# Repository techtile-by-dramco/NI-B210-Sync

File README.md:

# Methods to synchronise NI B210s for MIMO operation

This repository contains the B210 synchronization research code, hardware notes, and reproducible experiments. Start with the [experiment index](experiments/readme.md). The new RF work uses T04 as the common source and T05–T08 as the devices under test; it is split into state characterization (`50`), controlled coherent combining (`51`), and stability/recalibration events (`52`). Experiment `60` separately measures the ZMQ-to-Raspberry-Pi GPIO-arrival spread on one shared scope timebase. Each directory has a connection-first README and a `--dry-run` mode.

Repository layout:

- `experiments/` — acquisition, processing, results, and testbench instructions;
- `phased-locked-loop/` — PLL hardware, firmware, and control scripts;
- `octoclock-validation/` — reference-distribution validation;
- `software/` and `tests/` — prototypes and lower-level tests; and
- `manuscript/` — separate Overleaf Git checkout, intentionally ignored by this repository.

## Relevant sources
- [Synchronizing multiple AD9361 devices](https://wiki.analog.com/resources/eval/user-guides/ad-fmcomms5-ebz/multi-chip-sync?force_rev=1)
- [AD9361 Register Map Reference Manual](https://usermanual.wiki/Document/AD9361RegisterMapReferenceManualUG671.1082447504)
- [AD9361 Reference Manual (e.g., PLL architecture)](https://www.farnell.com/datasheets/2007082.pdf)
- [Schematic B210](https://files.ettus.com/schematics/b200/b210.pdf)
- [Schemetic octoclock CDA2990](https://files.ettus.com/schematics/octoclock/octoclock.pdf)
- [Ettus Research USRP FPGA HDL Source](https://github.com/EttusResearch/fpga)
- [AD community question related to phase diff](https://ez.analog.com/wide-band-rf-transceivers/design-support/f/q-a/543540/phase-difference-in-ad9361-multichip-synchronization)
- [Fractional/Integer-N PLL Basics](https://www.ti.com/lit/an/swra029/swra029.pdf)
- [FMComms5 Phase Synchronization](https://wiki.analog.com/resources/eval/user-guides/ad-fmcomms5-ebz/phase-sync)
- [Phase Difference in AD9361 Multichip Synchronization](https://ez.analog.com/wide-band-rf-transceivers/design-support/f/q-a/543540/phase-difference-in-ad9361-multichip-synchronization)
- [UHD Device synchronisation](https://files.ettus.com/manual/page_sync.html)
- [Timed commands in UHD](https://kb.ettus.com/index.php?title=Synchronizing_USRP_Events_Using_Timed_Commands_in_UHD)
- [DoA and methods to phase-align](https://www.youtube.com/watch?v=_UBPVi1vp2s&ab_channel=GNURadio)
- [Multichannel RF Reference Architecture](https://kb.ettus.com/Multichannel_RF_Reference_Architecture)
- [PLL-IC with phase synchronization](https://ez.analog.com/rf/f/q-a/165960/pll-ic-with-phase-synchronization/375973) (difference between sync and resync PLLs)
- [Phase-Locked Loops Enable Phase Alignment and Control](https://www.microwavejournal.com/articles/28830-phase-locked-loops-enable-phase-alignment-and-control)

## Relevant scientific publications
- [Multi-channel RF signal acquisition system design based on AD9361](https://ieeexplore.ieee.org/stamp/stamp.jsp?tp=&arnumber=9173310)
- [Angle of arrival estimation in a multi-antenna software defined radio system: impact of hardware and radio environment](https://link.springer.com/article/10.1007/s11276-022-03010-z)

## What needs to be synchronised for MIMO applications

At the RF transceiver:
- ADC/DAC sample clock
- RF mixer 
- Baseband digital clocks

At the FPGA:
- DSP (CORDICs)

Between FPGA and host:
- USB (to be checked)

At the host:

## Maintaining phase coherency at different PLLs

From [ref](https://ez.analog.com/cfs-file/__key/telligent-evolution-components-attachments/00-333-01-00-00-24-69-46/attachment.pdf):
Phase coherence is defined as the state in which two signals maintain a fixed phase relationship
between each other and is typically required for evaluating the performance of phased-array antennas
as well as for test and measurement equipment.
For integer-N PLLs, it is relatively straightforward to achieve phase coherence between multiple PLLs
by using the same reference for each PLL and updating each device at the same time to ensure the
PLL counters are aligned. This is often achieved by updating the PLL register contents with the new
frequency word while holding the device in reset. To ensure both parts get updated at the same time,
the reset signal is made common and so is cleared internally in the PLLs at exactly the same time.
This ensures the internal dividers in the PLL start counting from the same start-point. See here for a
good reference on achieving integer-N PLL phase coherence using this method. If the output
frequencies on both parts are updated at the same time then the consistent output phase will be
maintained between the multiple PLLs. To achieve absolute phase consistency with respect to the
reference input requires you to update the PLLs at a rate equal to an integer multiple of N-divide (PLL
feedback divider) times REFIN cycles. This would mean the reset signal would need to be
synchronized with the reference and a count done internally in a microcontroller to keep
synchronization. In many cases the absolute phase consistency is not required just that the relative
phase between the PLL outputs is kept constant. In this case LE can be asynchronous to the reference
input.

## B210

Sync input:
- pulse per second input: PPS_IN_EXT (see [Schematic B210](https://files.ettus.com/schematics/b200/b210.pdf))
- 20MHz reference input (as no GPS option to our B210): REFIN (see [Schematic B210](https://files.ettus.com/schematics/b200/b210.pdf))

The REFIN is connected to the [ADF4001](https://www.analog.com/en/products/adf4001.html) (200MHz Clock Generator PLL) which generates vcxo_tune which is connected to Voltage Controlled Temperature Compensated Crystal Oscillator (VCTCXO), which is than connected to a fan-out buffer to distribute it to xo_out (going to the AD9361) and xo_to_pll (to PLL RF in).

PPS_IN_EXT is connected to the Spartan6 IO_L34P_GCLK19_0.

PLL bring-up:
1. VCTCXO starts up
2. FX3 brings up transceiver, sets CLKOUT to FPGA
3. FX3 programs FPGA
4. FPGA writes to PLL, initializes PLL
5. PLL locks to external ref if avail.
6. If no ref, PLL tristated via SPI

## AD9361 - RF transceiver

As can be observed in the register manual and the [code](https://github.com/EttusResearch/uhd/blob/197cdc4f665cbd4e6394a7eeb44b405f67ab10b1/host/lib/usrp/common/ad9361_driver/ad9361_device.cpp#L1640). The BBPLL is unaltered wrt the reference PLL (40MHz) and RX and TX is multiplied by 2.
[AD9361 Register Map Reference Manual](https://usermanual.wiki/Document/AD9361RegisterMapReferenceManualUG671.1082447504)

### XTALN
The on-board 40MHz clock signal generated from the [ADF4001](https://www.analog.com/en/products/adf4001.html) is coherent:

### Synchronise ADC/DAC clocks
The ADC and DAC clocks can not be perfectly synchronised due to the divider, both clocks are derived from the same BBPLL.

$$ADC_{rate} = BBPLL_{rate} / 2^{div}$$

witd $div$ between 1 through 6. The value for $div$ is [determined so the the VCO rate is between 672MHz and 1430MHz](https://github.com/EttusResearch/uhd/blob/197cdc4f665cbd4e6394a7eeb44b405f67ab10b1/host/lib/usrp/common/ad9361_driver/ad9361_device.cpp#L1202).

The device utilizes a fractional-N synthesizer in the baseband PLL block to generate the desired sample rate for a given system. This synthesizer generates the ADC sample clock, DAC sample clock, and baseband digital clocks from any reference clock in the frequency range specified for the reference clock input.

## Sync BBPLLs and Digital CLK [AD9361 Register Map Reference Manual](https://usermanual.wiki/Document/AD9361RegisterMapReferenceManualUG671.1082447504)
  - SPI Register 0x001—Multichip Sync and Tx Monitor Control
  - D2—MCS BBPLL EnableTo synchronize the BBPLLs of multiple devices, write this bit high and then provide a sync pulse to SYNC_IN.
  - D1—MCS Digital CLK Enable To synchronize the digital clocks of multiple AD9361 devices, first synchronize the BBPLLs, then write this bit high and provide a sync pulse to the `SYNC_IN` pin. 
  - D0—MCS BB Enable Setting this bit enables the capability of baseband multichip digital synchronization. See also 0x001[D2:D1]. 

### Clock input options (from AD9361 datasheet)
The AD9361 operates using a reference clock that can be provided
by two different sources. The first option is to use a dedicated
crystal with a frequency between 19 MHz and 50 MHz connected
between the XTALP and XTALN pins. The second option is to
connect an external oscillator or clock distribution device (such as
the AD9548) to the XTALN pin (with the XTALP pin remaining
unconnected). If an external oscillator is used, the frequency
can vary between 10 MHz and 80 MHz. This reference clock
is used to supply the synthesizer blocks that generate all data
clocks, sample clocks, and local oscillators inside the device.
Errors in the crystal frequency can be removed by using the
digitally programmable digitally controlled crystal oscillator
(DCXO) function to adjust the on-chip variable capacitor. This
capacitor can tune the crystal frequency variance out of the
system, resulting in a more accurate reference clock from which
all other frequency signals are generated. This function can also
be used with on-chip temperature sensing to provide oscillator
frequency temperature compensation during normal operation.

### RF PLLs (from AD9361 datasheet)
The AD9361 contains two identical synthesizers to generate the
required LO signals for the RF signal paths:—one for the receiver
and one for the transmitter. Phase-locked loop (PLL) synthesizers
are fractional-N designs incorporating completely integrated
voltage controlled oscillators (VCOs) and loop filters. In TDD
operation, the synthesizers turn on and off as appropriate for the
RX and TX frames. In FDD mode, the TX PLL and the RX PLL
can be activated simultaneously. These PLLs require no external
components

#### RFPLL frequency

Scaling to [2xREF](https://github.com/EttusResearch/uhd/blob/197cdc4f665cbd4e6394a7eeb44b405f67ab10b1/host/lib/usrp/common/ad9361_driver/ad9361_device.cpp#L1640).
By setting registers `0x2AB` and `0x2AC`.

Meaning the RFPLL (F_{REF}) for TX and RX is 80MHz.

### BB PLL (from AD9361 datasheet)
The AD9361 also contains a baseband PLL synthesizer that is
used to generate all baseband related clock signals. These include
the ADC and DAC sampling clocks, the DATA_CLK signal (see
the Digital Data Interface section), and all data framing signals.
This PLL is programmed from 700 MHz to 1400 MHz based on
the data rate and sample rate requirements of the system. 

## FPGA

From [here](https://www.ni.com/nl-nl/shop/wireless-design-test/what-is-a-usrp-software-defined-radio/global-synchronization-and-clock-disciplining-with-ni-usrp-293x-.html):
- The USRP hardware OSP interpolates and up-converts the synthesized signals to 400 MS/s using a digital up conversion process, and uses the CORDIC algorithm to apply minor frequency offset corrections to achieve the requested RF center frequency. 
- The digitized I and Q data flow through parallel onboard signal processing (OSP) processes that applies DC offset correction and digital down conversion using the CORDIC algorithm.

[How to sync the CORDICs](https://files.ettus.com/manual/page_sync.html)

## UHD and GNURadio

There are four key elements required for phase coherent operation of resync-capable USRPs:

1. All USRPs share a common reference clock (10MHz Ref)
2. All USRPs share a common sense of time (PPS)
3. LO and DSP tuning is synchronous
4. Streaming is started synchronously

### Enable external PPS and 10MHz
```cpp
usrp->set_clock_source("external");
usrp->set_time_source("external");
```

### Defining a common absolute reference clock
The time can be 're'-set once a new PPS has occured:
```cpp
const uhd::time_spec_t last_pps_time = usrp->get_time_last_pps();
while (last_pps_time == usrp->get_time_last_pps()){
    //sleep 100 milliseconds (give or take)
}
// This command will be processed fairly soon after the last PPS edge:
usrp->set_time_next_pps(uhd::time_spec_t(0.0));

std::this_thread::sleep_for(std::chrono::milliseconds(1000));
```
After we reset the USRP's sense of time, we wait 1 second to ensure a PPS rising edge occurs and latches the 0.000s value to both USRPs. At this point, both USRPs should have a shared sense of time.  We've now satisfied the first and second requirements for phase coherent USRP operation. 

**TODO**: Send a command from the server to the RPIs to start resetting their time reference on next PPS. Or only start transmitting PPS signals from the octoclocks once all devices are operational (not sure the latter is supported by the Octoclock). 

### Timed commands for predicatable and repeatable phase offsets
```cp
usrp->clear_command_time();

usrp->set_command_time(usrp->get_time_now() + uhd::time_spec_t(0.1)); //set cmd time for .1s in the future

uhd::tune_request_t tune_request(freq);
usrp->set_rx_freq(tune_request);
std::this_thread::sleep_for(std::chrono::milliseconds(110)); //sleep 110ms (~10ms after retune occurs) to allow LO to lock

usrp->clear_command_time();
```
With the above code block, we are able to set a command time equal to the current time + 0.1s. Any commands that are called after `set_command_time()` will be sent to the USRP with a timestamp corresponding to the argument passed to `set_command_time()`. Because of this timestamp, the USRP will wait until the command time passes to execute the tune request. This will ensure that the LO and DSP chain of our USRPs are retuned synchronously (on the same clock cycle), satisfying the third requirement for phase coherent operation, i.e., LO and DSP tuning is synchronous.

Modern USRPs pass packets using the CHDR protocol. These packets can be used to issue commands to the USRP and may have an associated timestamp. A command with an included timestamp is called a timed command and it's important to understand how the USRP handles these timed commands. All blocks in a USRP's FPGA have a command queue and maintain a sense of time, however the Radio Core has the unique ability to store an absolute sense of time known as the vita_time. When timed commands are issued to the USRP, they are added to a command FIFO of finite depth and are executed when the timestamp in the header of the command packet is >= the RFNoC block's sense of time. Utilizing these timed commands correctly allows for various USRP functionality to be executed with nanosecond precision, enabling time and phase coherent operation across multiple devices.

#### Command Queue
As commands are passed from host to USRP, they are added to a FIFO on the USRP's FPGA. This FIFO is called the command queue and all commands that are sent to the USRP must pass through a command queue. Each block in the FPGA that handles data also has its own command queue. The command queue FIFO is not to be confused with the data FIFOs used to buffer data between blocks (pictured in Figure 3).

Every command queue maintains a sense of time. The mechanism for acquiring this sense of time is different between the Radio Core and other IP cores (including custom RFNoC blocks) and will be explored later in this application note. When commands enter the command queue, their timestamp is compared against the command queue's sense of time and the commands are executed when Queue Time >= Command Time. Commands without timestamps are executed immediately when they're at the front of the queue. Command queues in the USRP do not support on-the-fly reordering, meaning a command at the front of the queue will block subsequent commands from executing even if their timestamp has passed.

Every IP core on a USRP, including the Radio Core, DDC, DUC, and custom blocks, includes one command queue per data stream (certain blocks are designed to pass multiple data streams). The depth of this command queue varies from device to device is determined at FPGA compilation time based on user settings and available resources. An overflow of the command queue will result in a system halt and often requires a physical reset of the FPGA.

The B210 (Xilinx Spartan 6 XC6SLX150) has by default a depth of 8 (radio core) and 5 (IP cores).

### Phase-aligned DSP
In order to achieve phase alignment between USRP devices, the CORDICS in both devices must be aligned with respect to each other. This is easily achieved by issuing stream commands with a time spec property, which instructs the streaming to begin at a specified time. Since the devices are already synchronized via the 10 MHz and PPS inputs, the streaming will start at exactly the same time on both devices. The CORDICs are reset at each start-of-burst command, so users should ensure that every start-of-burst also has a time spec set.

#### Receive example

##### One burst
```cpp
uhd::stream_cmd_t stream_cmd(uhd::stream_cmd_t::STREAM_MODE_NUM_SAMPS_AND_DONE); 
stream_cmd.num_samps = samps_to_recv;
stream_cmd.stream_now = false;
stream_cmd.time_spec = uhd::time_spec_t(usrp->get_time_now() + uhd::time_spec_t(1.0));
usrp->issue_stream_cmd(stream_cmd);
```

##### Streaming
```cpp
// create a receive streamer
uhd::stream_args_t stream_args("fc32", wire); // complex floats
stream_args.channels             = "0,1,2,3";
uhd::rx_streamer::sptr rx_stream = usrp->get_rx_stream(stream_args);

// setup streaming
uhd::stream_cmd_t stream_cmd(uhd::stream_cmd_t::STREAM_MODE_START_CONTINUOUS);
stream_cmd.stream_now = false;
stream_cmd.time_spec  = uhd::time_spec_t(usrp->get_time_now() + uhd::time_spec_t(1.0));
rx_stream->issue_stream_cmd(stream_cmd);
```

Our system will begin to stream data 1s after the time returned by usrp->get_time_now(). Data sent to the host will be phase coherent between the 4 RX channels in this system. 
**TODO**: Check if the signal maintains a known phase relationship between both i) the channels and ii) the devices, across runs of code and system power cycles.

#### Transmit example
```cpp
uhd::tx_metadata_t md; //the metadata incl. the time spec
md.start_of_burst = true;
md.end_of_burst = false;
md.has_time_spec = true;
md.time_spec = time_to_send;
//send a single packet
size_t num_tx_samps = tx_streamer->send(buffs, samps_to_send, md);
```

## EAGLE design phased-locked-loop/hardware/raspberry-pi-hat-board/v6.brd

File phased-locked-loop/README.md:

# Techtile PLL board ✅

This PCB was developed by Guus Leenders from KU Leuven, in collaboration with DRAMCO, with assistance from Jarne Van Mulders. The board is utilized in a distributed antenna or **Radioweave** infrastructure and delivers a phase-synchronous RF output to the USRP by means of a PPS and 10MHz signal. This board is specifically designed for the USRP B210 by Ettus.

The PPS and 10MHz signals (coming from the octoclocks CDA2990) are amplified using on board buffers and are connected to the
* PLL IC (MAX287x) ❗❗ **--> allowing for ∿ phase synchronisation ∿**
* the flat cable connector (given that the raspberry pi also has access to these signals) ❗
* the input SMA connectors of the USRPs intself ❗❗
  * ** 10 MHz --> ∿ frequency synchronisation ∿ for internal (RF) PLLs**
  * ** PPS --> ⏰ time synchronisation ⏰**

The board is controlled via I2C commands and features a flat cable input connected to the RPI HAT (developed by DRAMCO) to drive the PLL output. The most important registers are displayed below.

###  PLL board general settings ⚙️

|Register name| byte |
|--|--|
|REGISTER_SETTINGS_DEVICE_ID            | 0x00 |
|REGISTER_SETTINGS_HARDWARE_VERSION     | 0x01 |
|REGISTER_SETTINGS_FIRMWARE_VERSION     | 0x02 |
|REGISTER_SETTINGS_SAVE_TO_EEPROM       | 0x03 |
|REGISTER_SETTINGS_PLL_REFERENCE_CLOCK  | 0x04 |
|REGISTER_SETTINGS_PLL_REFERENCE_DIVIDER| 0x06 |
|REGISTER_SETTINGS_LED_MODE             | 0x07 |
|REGISTER_SETTINGS_LED_BLINK_ON_TIME    | 0x08 |
|REGISTER_SETTINGS_LED_BLINK_OFF_TIME   | 0x09 |

###  PLL (MAX287x) settings ⚙️

|Register name| byte | Remarks |
|--|--|--|
|REGISTER_PLL_POWER                     | 0x10 | |
|REGISTER_PLL_FREQUENCY                 | 0x11 | 2 byte (uint16) |
|REGISTER_PLL_ENABLE_OUTPUT             | 0x13 | |
|REGISTER_PLL_LOCK_DETECTED             | 0x14 | Read only |
|REGISTER_PLL_MODE                      | 0x15 | Read only |

# Phase synchronisation in Techtile ToDo 📝
- Work further on python script to achieve phase-synchronised outputs with the B210 USRP. Validate and visualize the signals on the oscilloscope by using two separate setups consisting of RPI, USRP, PLL, PPS, and 10 MHz input.
- Current status ⏳ PENDING ⏳

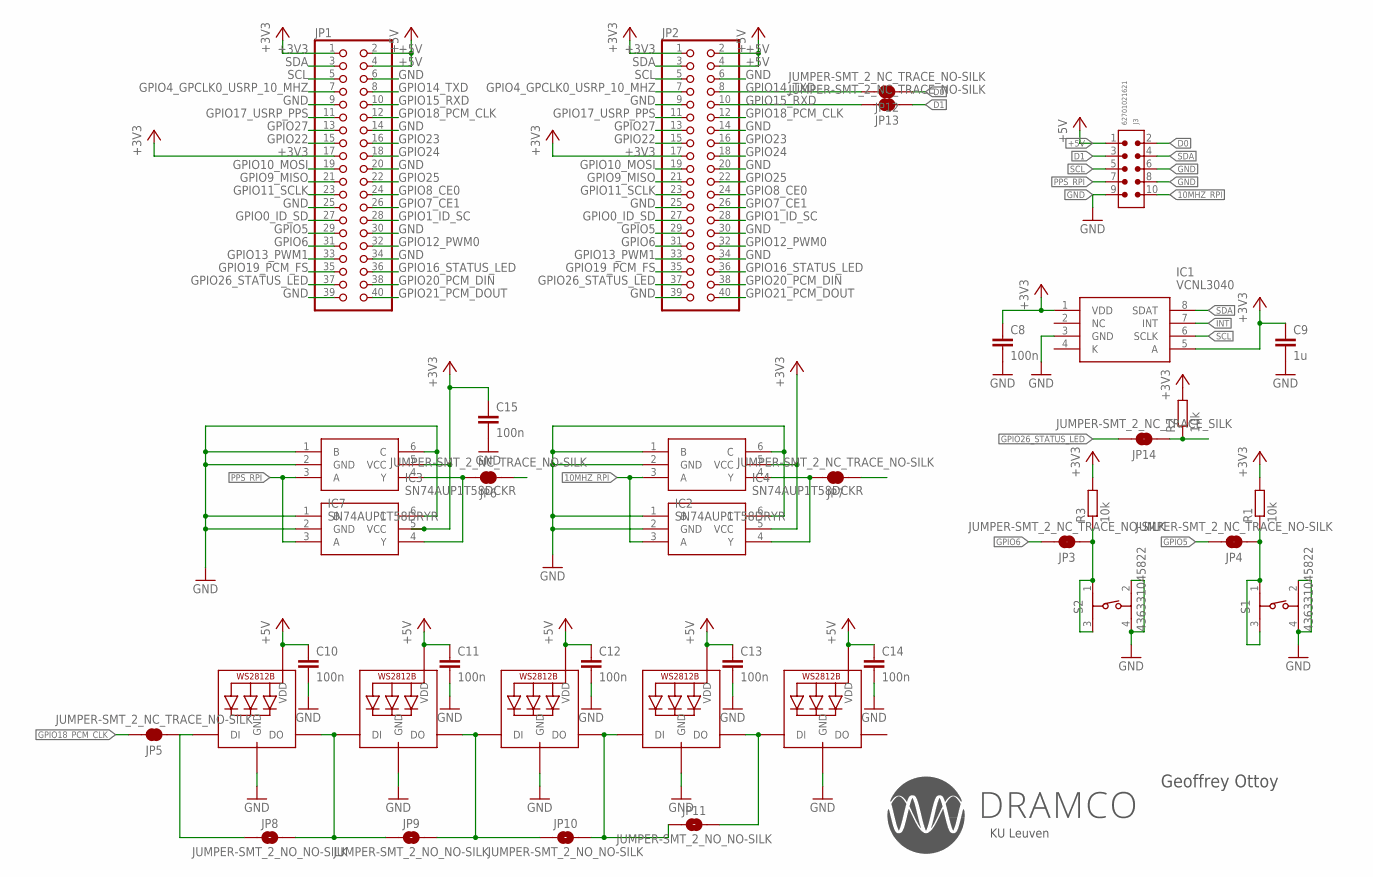
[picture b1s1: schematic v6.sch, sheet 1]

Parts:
C8, C10, C11, C12, C13, C14, C15: 100n; C0603
C9: 1u; C0603
IC1: VCNL3040; SON108P200X400X115-8N
IC2, IC7: SN74AUP1T58DRYR; SON50P100X145X60-6N
IC3, IC4: SN74AUP1T58DCKR; SOT65P210X110-6N
J3: 62701021621
JP1: PINHD-2X20; 2X20
JP2: PINHD-2X20/90; 2X20/90
JP3, JP4, JP5, JP6, JP7, JP12, JP13: JUMPER-SMT_2_NC_TRACE_NO-SILK; SMT-JUMPER_2_NC_TRACE_NO-SILK
JP8, JP9, JP10, JP11: JUMPER-SMT_2_NO_NO-SILK; SMT-JUMPER_2_NO_NO-SILK
JP14: JUMPER-SMT_2_NC_TRACE_SILK; SMT-JUMPER_2_NC_TRACE_SILK
LED1, LED2, LED3, LED4, LED5: WS2812B5050; WS2812B
R1, R2, R3: 10k; R0603
S1, S2: 436331045822; 4363X10458XX

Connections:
10MHZ_RPI: IC2.3 (A), IC4.3 (A), J3.10
+3V3: C8.1, C9.1, C15.1, IC1.1 (VDD), IC1.5 (A), IC2.5 (VCC), IC3.5 (VCC), IC4.5 (VCC), IC7.5 (VCC), JP1.1, JP1.17, JP2.1, JP2.17, R1.2, R2.2, R3.2
+5V: C10.1, C11.1, C12.1, C13.1, C14.1, J3.1, JP1.2, JP1.4, JP2.2, JP2.4, LED1.1-VDD (VDD), LED2.1-VDD (VDD), LED3.1-VDD (VDD), LED4.1-VDD (VDD), LED5.1-VDD (VDD)
D0: J3.2, JP12.1
D1: J3.3, JP13.1
GND: C8.2, C9.2, C10.2, C11.2, C12.2, C13.2, C14.2, C15.2, IC1.3 (GND), IC2.1 (B), IC2.2 (GND), IC2.6 (C), IC3.1 (B), IC3.2 (GND), IC3.6 (C), IC4.1 (B), IC4.2 (GND), IC4.6 (C), IC7.1 (B), IC7.2 (GND), IC7.6 (C), J3.6, J3.8, J3.9, JP1.6, JP1.9, JP1.14, JP1.20, JP1.25, JP1.30, JP1.34, JP1.39, JP2.6, JP2.9, JP2.14, JP2.20, JP2.25, JP2.30, JP2.34, JP2.39, LED1.3-GND (GND), LED2.3-GND (GND), LED3.3-GND (GND), LED4.3-GND (GND), LED5.3-GND (GND), S1.2 (4), S1.4 (2), S2.2 (4), S2.4 (2); also elsewhere on the board
GPIO0_ID_SD: JP1.27, JP2.27
GPIO1_ID_SC: JP1.28, JP2.28
GPIO4_GPCLK0_USRP_10_MHZ: JP1.7, JP2.7, JP7.1
GPIO5: JP1.29, JP2.29, JP4.2
GPIO6: JP1.31, JP2.31, JP3.2
GPIO7_CE1: JP1.26, JP2.26
GPIO8_CE0: JP1.24, JP2.24
GPIO9_MISO: JP1.21, JP2.21
GPIO10_MOSI: JP1.19, JP2.19
GPIO11_SCLK: JP1.23, JP2.23
GPIO12_PWM0: JP1.32, JP2.32
GPIO13_PWM1: JP1.33, JP2.33
GPIO14_TXD: JP1.8, JP2.8, JP12.2
GPIO15_RXD: JP1.10, JP2.10, JP13.2
GPIO16_STATUS_LED: JP1.36, JP2.36
GPIO17_USRP_PPS: JP1.11, JP2.11, JP6.1
GPIO18_PCM_CLK: JP1.12, JP2.12, JP5.2
GPIO19_PCM_FS: JP1.35, JP2.35
GPIO20_PCM_DIN: JP1.38, JP2.38
GPIO21_PCM_DOUT: JP1.40, JP2.40
GPIO22: JP1.15, JP2.15
GPIO23: JP1.16, JP2.16
GPIO24: JP1.18, JP2.18
GPIO25: JP1.22, JP2.22
GPIO26_STATUS_LED: JP1.37, JP2.37, JP14.2
GPIO27: JP1.13, JP2.13
INT: IC1.7 (INT), JP14.1, R2.1
unnamed: IC3.4 (Y), IC7.4 (Y), JP6.2
unnamed: IC2.4 (Y), IC4.4 (Y), JP7.2
unnamed: JP3.1, R3.1, S2.1 (3), S2.3 (1)
unnamed: JP8.2, JP9.1, LED1.2-DOUT (DO), LED2.4-DIN (DI)
unnamed: JP9.2, JP10.1, LED2.2-DOUT (DO), LED3.4-DIN (DI)
unnamed: JP10.2, JP11.1, LED3.2-DOUT (DO), LED4.4-DIN (DI)
unnamed: JP11.2, LED4.2-DOUT (DO), LED5.4-DIN (DI)
unnamed: JP4.1, R1.1, S1.1 (3), S1.3 (1)
unnamed: JP5.1, JP8.1, LED1.4-DIN (DI)
PPS_RPI: IC3.3 (A), IC7.3 (A), J3.7
SCL: IC1.6 (SCLK), J3.5, JP1.5, JP2.5; also elsewhere on the board
SDA: IC1.8 (SDAT), J3.4, JP1.3, JP2.3; also elsewhere on the board

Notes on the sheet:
Geoffrey Ottoy
KU Leuven

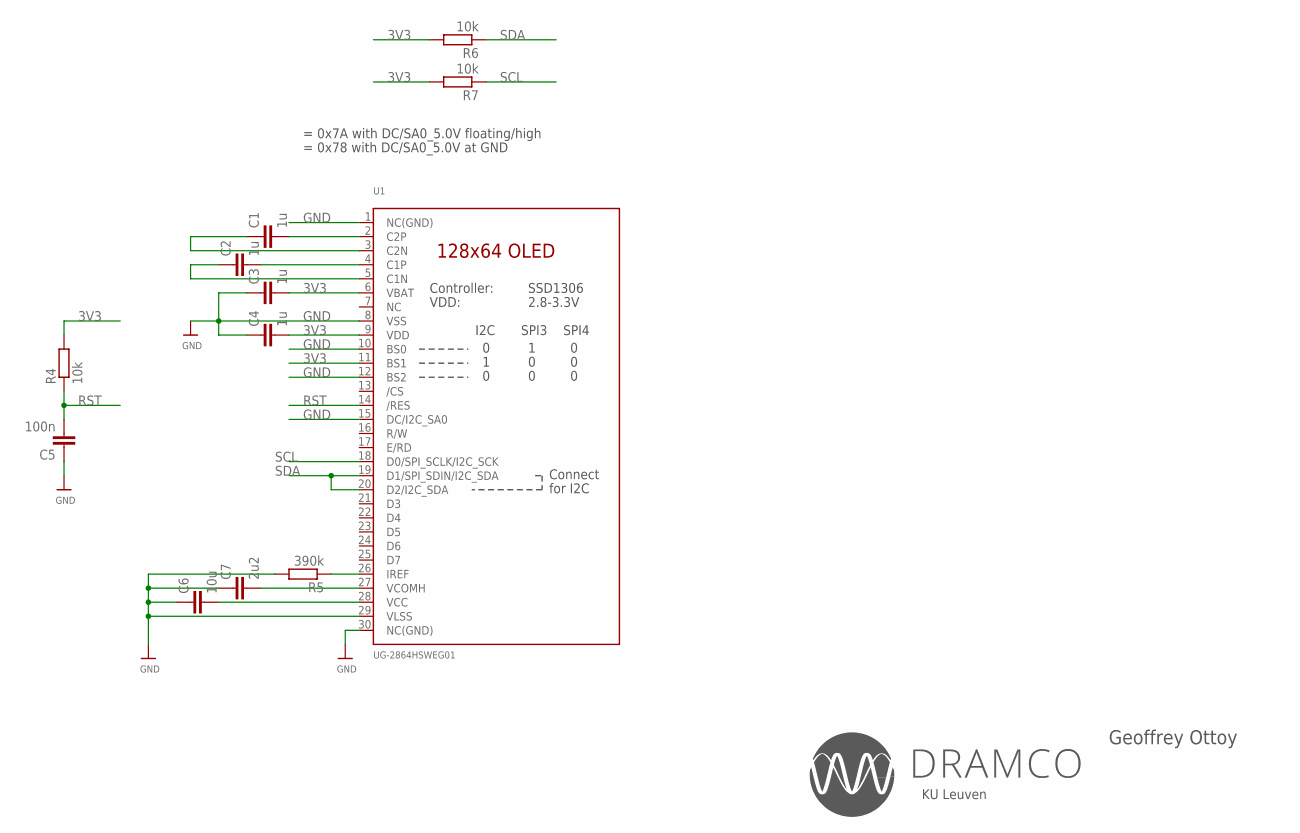
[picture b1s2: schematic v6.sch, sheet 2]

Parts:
C1, C2, C3, C4: 1u; C0603
C5: 100n; C0603
C6: 10u; C0603
C7: 2u2; C0603
R4, R6, R7: 10k; R0603
R5: 390k; R0603
U1: UG-2864HSWEG01; UG-2864HSWEG01_0.96IN_WRAPAROUND

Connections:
3V3: C3.2, C4.2, R4.2, R6.2, R7.2, U1.6 (VBAT), U1.9 (VDD), U1.11 (BS1)
GND: C3.1, C4.1, C5.1, C6.1, C7.1, R5.2, U1.1 (NC(GND)), U1.8 (VSS), U1.10 (BS0), U1.12 (BS2), U1.15 (DC/I2C_SA0), U1.29 (VLSS), U1.30 (NC(GND)); also elsewhere on the board
unnamed: C1.2, U1.2 (C2P)
unnamed: C6.2, U1.28 (VCC)
unnamed: C7.2, U1.27 (VCOMH)
unnamed: R5.1, U1.26 (IREF)
unnamed: C1.1, U1.3 (C2N)
unnamed: C2.2, U1.4 (C1P)
unnamed: C2.1, U1.5 (C1N)
RST: C5.2, R4.1, U1.14 (/RES)
SCL: R7.1, U1.18 (D0/SPI_SCLK/I2C_SCK); also elsewhere on the board
SDA: R6.1, U1.19 (D1/SPI_SDIN/I2C_SDA), U1.20 (D2/I2C_SDA); also elsewhere on the board

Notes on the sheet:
= 0x7A with DC/SA0_5.0V floating/high
= 0x78 with DC/SA0_5.0V at GND
Geoffrey Ottoy
KU Leuven

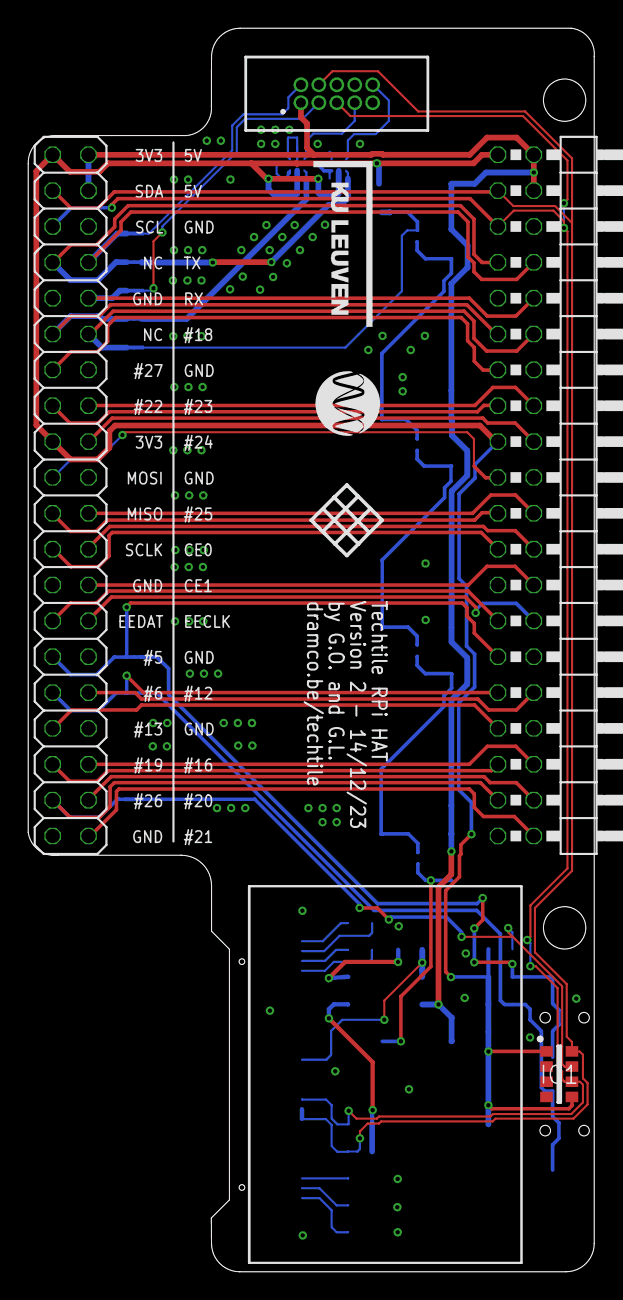
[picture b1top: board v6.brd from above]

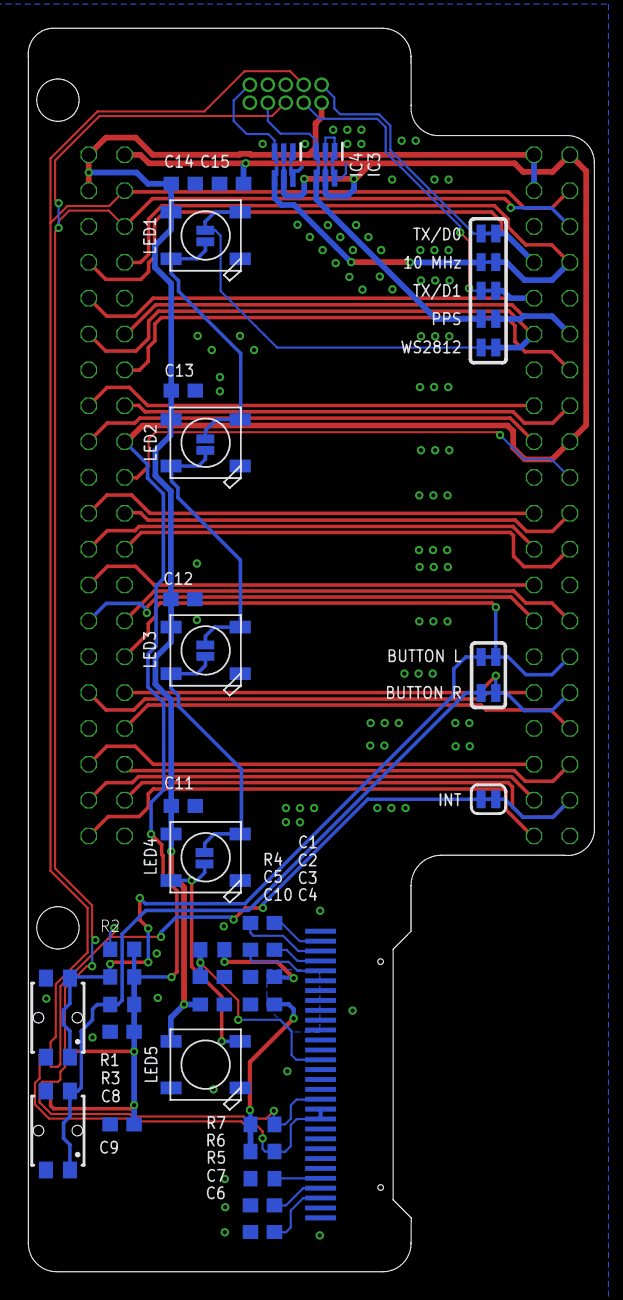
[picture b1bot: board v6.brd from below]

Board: 2 copper layers, 40.1 x 88.1 mm, 50 parts (45 on the bottom side), 54 nets.

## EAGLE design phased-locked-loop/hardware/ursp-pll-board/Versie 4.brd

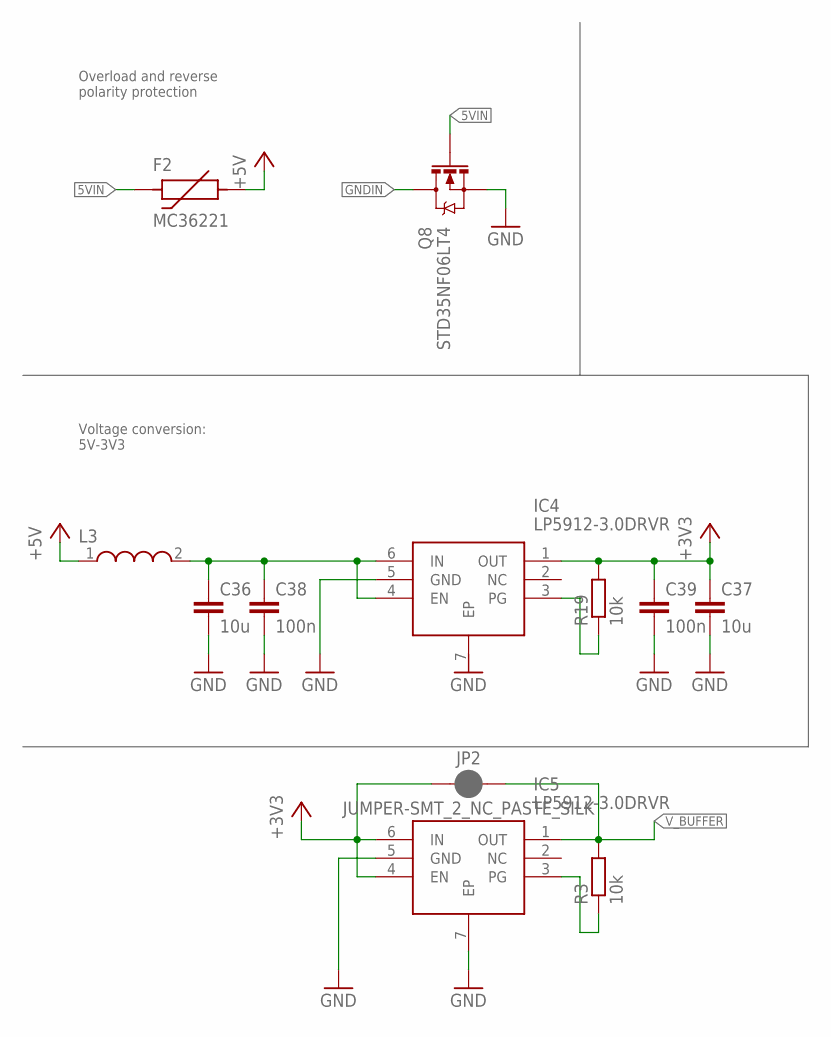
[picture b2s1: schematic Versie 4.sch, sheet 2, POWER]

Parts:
C36, C37: 10u; C0603
C38, C39: 100n; C0603
F2: MC36221; 1206
IC4, IC5: LP5912-3.0DRVR; SON65P200X200X80-7N
JP2: JUMPER-SMT_2_NC_PASTE_SILK; SMT-JUMPER_2_NC_PASTE_SILK
L3: WE-CBA_0603(WB/HS); WE-CBA_0603(W=2.2)
Q8: STD35NF06LT4; SOT23-3
R3, R19: 10k; R0603

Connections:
5VIN: F2.P$1, Q8.1 (G); also elsewhere on the board
+3V3: C37.1, C39.1, IC4.1 (OUT), IC5.4 (EN), IC5.6 (IN), JP2.1, R19.2; also elsewhere on the board
+5V: F2.P$2, L3.1
GND: C36.2, C37.2, C38.2, C39.2, IC4.5 (GND), IC5.5 (GND), IC5.7 (EP), Q8.2 (S); also elsewhere on the board
GNDIN: Q8.3 (D); also elsewhere on the board
unnamed: IC5.3 (PG), R3.1
unnamed: C36.1, C38.1, IC4.4 (EN), IC4.6 (IN), L3.2
unnamed: IC4.3 (PG), R19.1
V_BUFFER: IC5.1 (OUT), JP2.2, R3.2; also elsewhere on the board

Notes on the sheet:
Overload and reverse polarity protection
Voltage conversion: 5V-3V3

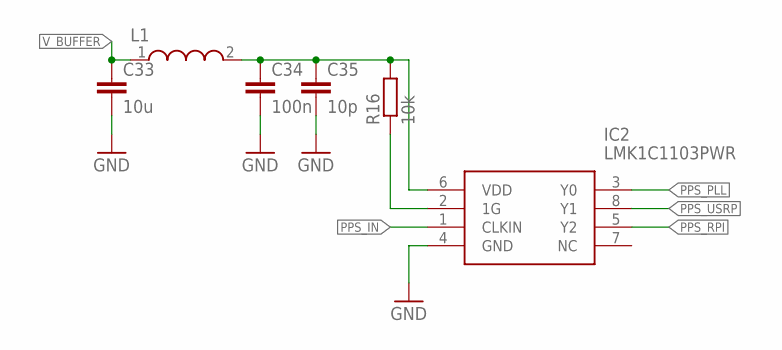
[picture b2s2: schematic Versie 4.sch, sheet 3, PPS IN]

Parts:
C33: 10u; C0603
C34: 100n; C0603
C35: 10p; C0603
IC2: LMK1C1103PWR; SOP65P640X120-8N
L1: WE-CBA_0603(WB/HS); WE-CBA_0603(W=2.2)
R16: 10k; R0603

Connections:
GND: C33.2, C34.2, C35.2, IC2.4 (GND); also elsewhere on the board
unnamed: IC2.2 (1G), R16.1
unnamed: C34.1, C35.1, IC2.6 (VDD), L1.2, R16.2
PPS_IN: IC2.1 (CLKIN); also elsewhere on the board
PPS_PLL: IC2.3 (Y0); also elsewhere on the board
PPS_RPI: IC2.5 (Y2); also elsewhere on the board
PPS_USRP: IC2.8 (Y1); also elsewhere on the board
V_BUFFER: C33.1, L1.1; also elsewhere on the board

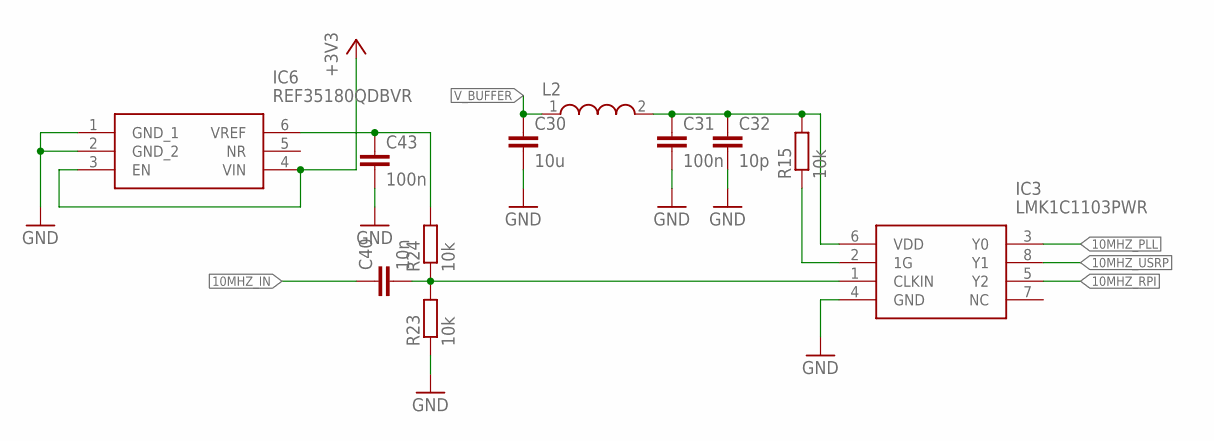
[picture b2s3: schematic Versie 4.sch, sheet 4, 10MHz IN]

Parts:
C30: 10u; C0603
C31, C43: 100n; C0603
C32: 10p; C0603
C40: 10n; C0603
IC3: LMK1C1103PWR; SOP65P640X120-8N
IC6: REF35180QDBVR; SOT95P280X145-6N
L2: WE-CBA_0603(WB/HS); WE-CBA_0603(W=2.2)
R15, R23, R24: 10k; R0603

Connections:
10MHZ_IN: C40.1; also elsewhere on the board
10MHZ_PLL: IC3.3 (Y0); also elsewhere on the board
10MHZ_RPI: IC3.5 (Y2); also elsewhere on the board
10MHZ_USRP: IC3.8 (Y1); also elsewhere on the board
+3V3: IC6.3 (EN), IC6.4 (VIN); also elsewhere on the board
GND: C30.2, C31.2, C32.2, C43.2, IC3.4 (GND), IC6.1 (GND_1), IC6.2 (GND_2), R23.1; also elsewhere on the board
unnamed: C40.2, IC3.1 (CLKIN), R23.2, R24.1
unnamed: IC3.2 (1G), R15.1
unnamed: C31.1, C32.1, IC3.6 (VDD), L2.2, R15.2
unnamed: C43.1, IC6.6 (VREF), R24.2
V_BUFFER: C30.1, L2.1; also elsewhere on the board

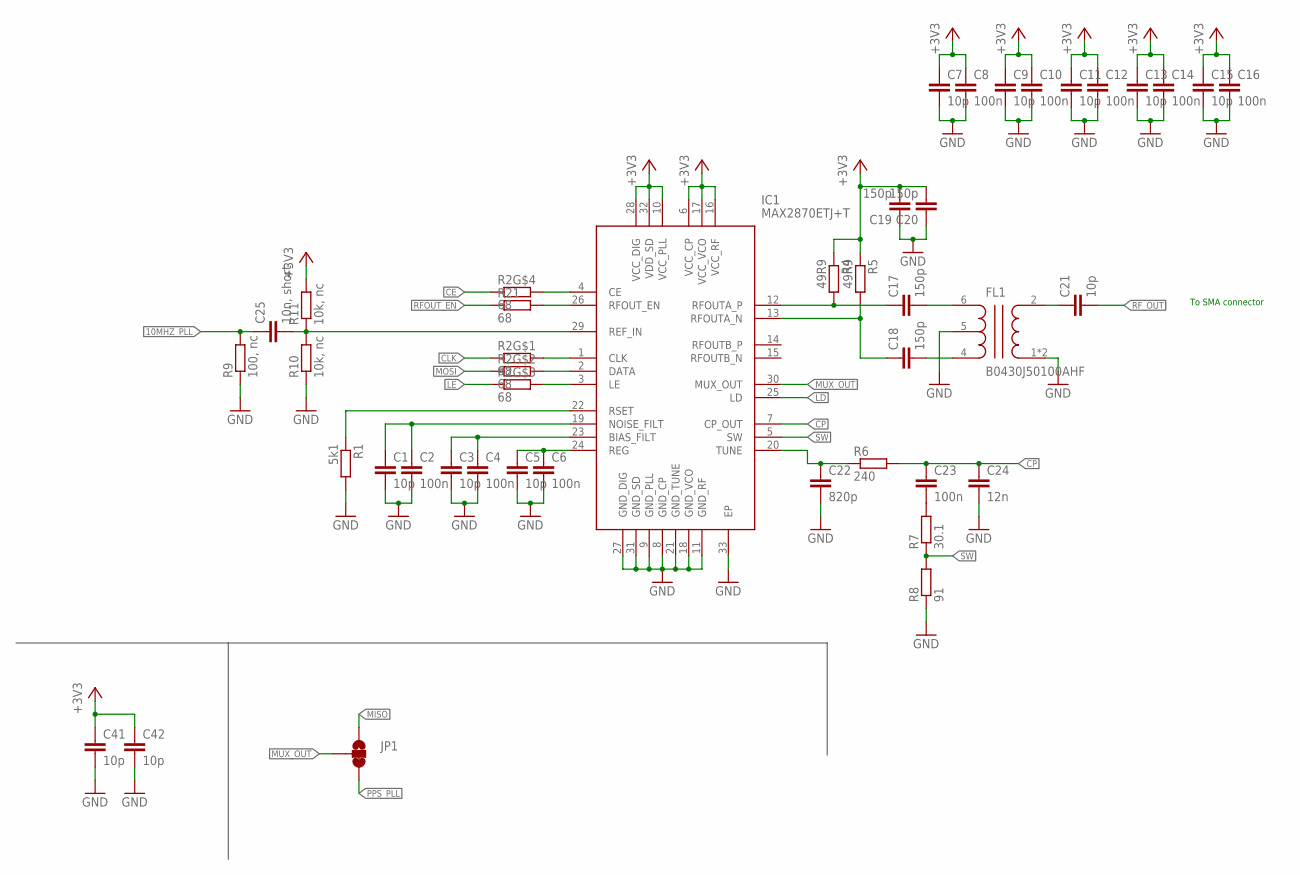
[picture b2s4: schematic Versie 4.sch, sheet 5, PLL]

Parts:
C1, C3, C5, C7, C9, C11, C13, C15, C41, C42: 10p; C0603
C2, C4, C6, C8, C10, C12, C14, C16, C23: 100n; C0603
C17, C18, C19, C20: 150p; C0402
C21: 10p; C0402
C22: 820p; C0603
C24: 12n; C0603
C25: 10n, short; C0603
FL1: B0430J50100AHF
IC1: MAX2870ETJ+T; QFN50P500X500X80-33N
JP1: JUMPER-SMT_3_1-NC_TRACE_SILK; SMT-JUMPER_3_1-NC_TRACE_SILK
R1: 5k1; R0603
R2: 68; CAY16A1003F4LF
R4, R5: 49R9; R0402
R6: 240; R0603
R7: 30.1; R0603
R8: 91; R0603
R9: 100, nc; R0603
R10, R11: 10k, nc; R0603
R21: 68; R0603

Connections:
10MHZ_PLL: C25.1, R9.2; also elsewhere on the board
+3V3: C7.1, C8.1, C9.1, C10.1, C11.1, C12.1, C13.1, C14.1, C15.1, C16.1, C19.2, C20.2, C41.1, C42.1, IC1.6 (VCC_CP), IC1.10 (VCC_PLL), IC1.16 (VCC_RF), IC1.17 (VCC_VCO), IC1.28 (VCC_DIG), IC1.32 (VDD_SD), R4.1, R5.1, R11.2; also elsewhere on the board
CE: R2.4 (1); also elsewhere on the board
CLK: R2.1; also elsewhere on the board
CP: C23.1, C24.1, IC1.7 (CP_OUT), R6.2
GND: C1.2, C2.2, C3.2, C4.2, C5.2, C6.2, C7.2, C8.2, C9.2, C10.2, C11.2, C12.2, C13.2, C14.2, C15.2, C16.2, C19.1, C20.1, C22.2, C24.2, C41.2, C42.2, FL1.1 (GND_1), FL1.3 (GND_1), FL1.5 (NC), IC1.8 (GND_CP), IC1.9 (GND_PLL), IC1.11 (GND_RF), IC1.18 (GND_VCO), IC1.21 (GND_TUNE), IC1.27 (GND_DIG), IC1.31 (GND_SD), IC1.33 (EP), R1.2, R8.1, R9.1, R10.1; also elsewhere on the board
LD: IC1.25 (LD); also elsewhere on the board
LE: R2.3 (1); also elsewhere on the board
MISO: JP1.1; also elsewhere on the board
MOSI: R2.2 (1); also elsewhere on the board
MUX_OUT: IC1.30 (MUX_OUT), JP1.2
unnamed: C5.1, C6.1, IC1.24 (REG)
unnamed: IC1.22 (RSET), R1.1
unnamed: IC1.1 (CLK), R2.8 (2)
unnamed: IC1.2 (DATA), R2.7 (2)
unnamed: IC1.3 (LE), R2.6 (2)
unnamed: C1.1, C2.1, IC1.19 (NOISE_FILT)
unnamed: C3.1, C4.1, IC1.23 (BIAS_FILT)
unnamed: IC1.26 (RFOUT_EN), R21.2
unnamed: IC1.4 (CE), R2.5 (2)
unnamed: C22.1, IC1.20 (TUNE), R6.1
unnamed: C17.1, IC1.12 (RFOUTA_P), R4.2
unnamed: C18.1, IC1.13 (RFOUTA_N), R5.2
unnamed: C18.2, FL1.4 (BALANCED_PORT_1)
unnamed: C17.2, FL1.6 (BALANCED_PORT_2)
unnamed: C23.2, R7.2
unnamed: C25.2, IC1.29 (REF_IN), R10.2, R11.1
unnamed: C21.1, FL1.2 (UNBALANCED)
PPS_PLL: JP1.3; also elsewhere on the board
RFOUT_EN: R21.1; also elsewhere on the board
RF_OUT: C21.2; also elsewhere on the board
SW: IC1.5 (SW), R7.1, R8.2

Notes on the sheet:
To SMA connector

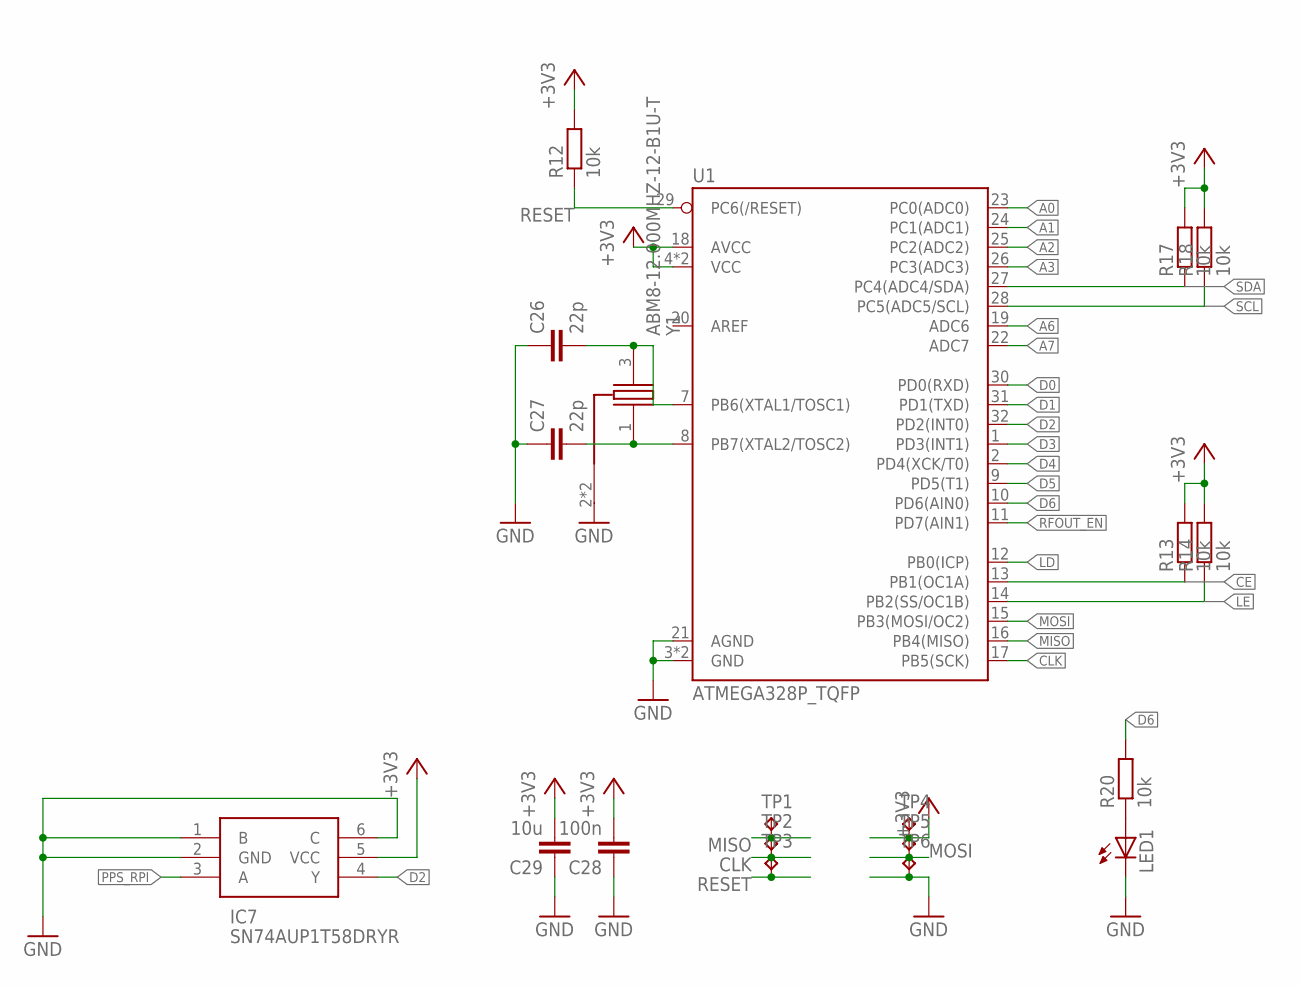
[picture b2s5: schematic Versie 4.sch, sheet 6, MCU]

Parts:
C26, C27: 22p; C0603
C28: 100n; C0603
C29: 10u; C0603
IC7: SN74AUP1T58DRYR; SON50P100X145X60-6N
LED1: LEDCHIPLED_0603; CHIPLED_0603
R12, R13, R14, R17, R18, R20: 10k; R0603
TP1, TP2, TP3, TP4, TP5, TP6: TPTP16R; TP16R
U1: ATMEGA328P_TQFP; TQFP32-08
Y1: ABM8-12.000MHZ-12-B1U-T; ABM810000MHZ12D2W

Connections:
+3V3: C28.2, C29.2, IC7.5 (VCC), R12.2, R13.2, R14.2, R17.2, R18.2, TP4.TP, U1.4 (VCC), U1.6 (VCC), U1.18 (AVCC); also elsewhere on the board
A0: U1.23 (PC0(ADC0)); also elsewhere on the board
A1: U1.24 (PC1(ADC1)); also elsewhere on the board
A2: U1.25 (PC2(ADC2)); also elsewhere on the board
A3: U1.26 (PC3(ADC3)); also elsewhere on the board
A6: U1.19 (ADC6); also elsewhere on the board
A7: U1.22 (ADC7); also elsewhere on the board
CE: R13.1, U1.13 (PB1(OC1A)); also elsewhere on the board
CLK: TP2.TP, U1.17 (PB5(SCK)); also elsewhere on the board
D0: U1.30 (PD0(RXD)); also elsewhere on the board
D1: U1.31 (PD1(TXD)); also elsewhere on the board
D2: IC7.4 (Y), U1.32 (PD2(INT0))
D3: U1.1 (PD3(INT1))
D4: U1.2 (PD4(XCK/T0))
D5: U1.9 (PD5(T1))
D6: R20.2, U1.10 (PD6(AIN0))
GND: C26.1, C27.1, C28.1, C29.1, IC7.1 (B), IC7.2 (GND), IC7.6 (C), LED1.C, TP6.TP, U1.3 (GND), U1.5 (GND), U1.21 (AGND), Y1.2 (GND_1), Y1.4 (GND_1); also elsewhere on the board
LD: U1.12 (PB0(ICP)); also elsewhere on the board
LE: R14.1, U1.14 (PB2(SS/OC1B)); also elsewhere on the board
MISO: TP1.TP, U1.16 (PB4(MISO)); also elsewhere on the board
MOSI: TP5.TP, U1.15 (PB3(MOSI/OC2)); also elsewhere on the board
unnamed: LED1.A, R20.1
unnamed: C26.2, U1.7 (PB6(XTAL1/TOSC1)), Y1.3 (X2)
unnamed: C27.2, U1.8 (PB7(XTAL2/TOSC2)), Y1.1 (X1)
PPS_RPI: IC7.3 (A); also elsewhere on the board
RESET: R12.1, TP3.TP, U1.29 (PC6(/RESET))
RFOUT_EN: U1.11 (PD7(AIN1)); also elsewhere on the board
SCL: R18.1, U1.28 (PC5(ADC5/SCL)); also elsewhere on the board
SDA: R17.1, U1.27 (PC4(ADC4/SDA)); also elsewhere on the board

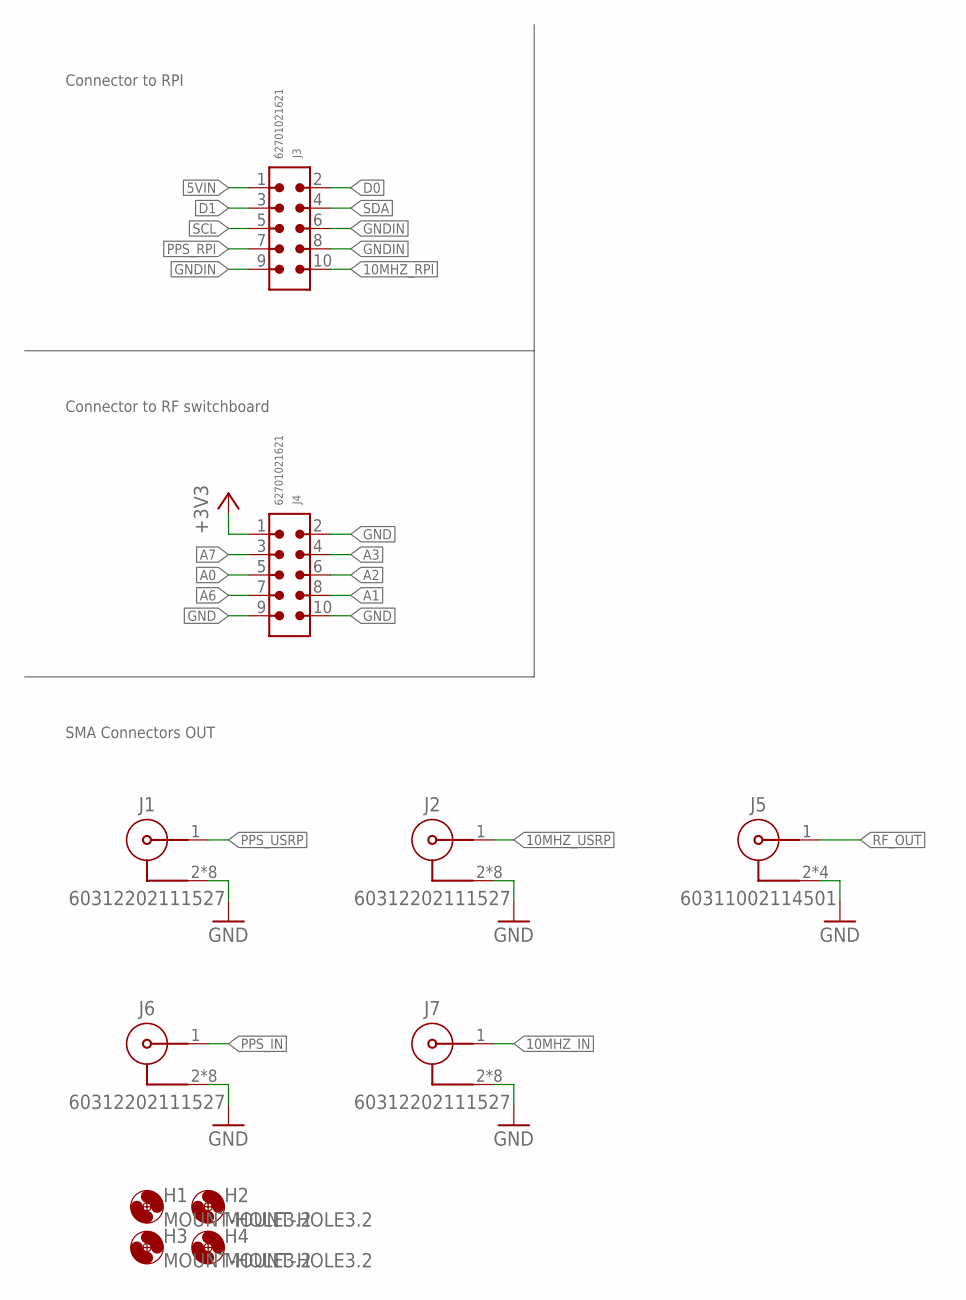
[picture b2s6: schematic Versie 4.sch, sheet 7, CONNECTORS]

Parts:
H1, H2, H3, H4: MOUNT-HOLE3.2; 3,2
J1, J2, J6, J7: 60312202111527
J3, J4: 62701021621
J5: 60311002114501

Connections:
5VIN: J3.1; also elsewhere on the board
10MHZ_IN: J7.1; also elsewhere on the board
10MHZ_RPI: J3.10; also elsewhere on the board
10MHZ_USRP: J2.1; also elsewhere on the board
+3V3: J4.1; also elsewhere on the board
A0: J4.5; also elsewhere on the board
A1: J4.8; also elsewhere on the board
A2: J4.6; also elsewhere on the board
A3: J4.4; also elsewhere on the board
A6: J4.7; also elsewhere on the board
A7: J4.3; also elsewhere on the board
D0: J3.2; also elsewhere on the board
D1: J3.3; also elsewhere on the board
GND: J1.2, J1.3 (2), J1.4 (2), J1.5 (2), J1.7 (2), J1.8 (2), J1.9 (2), J1.10 (2), J2.2, J2.3 (2), J2.4 (2), J2.5 (2), J2.7 (2), J2.8 (2), J2.9 (2), J2.10 (2), J4.2, J4.9, J4.10, J5.2, J5.3 (2), J5.4 (2), J5.5 (2), J6.2, J6.3 (2), J6.4 (2), J6.5 (2), J6.7 (2), J6.8 (2), J6.9 (2), J6.10 (2), J7.2, J7.3 (2), J7.4 (2), J7.5 (2), J7.7 (2), J7.8 (2), J7.9 (2), J7.10 (2); also elsewhere on the board
GNDIN: J3.6, J3.8, J3.9; also elsewhere on the board
PPS_IN: J6.1; also elsewhere on the board
PPS_RPI: J3.7; also elsewhere on the board
PPS_USRP: J1.1; also elsewhere on the board
RF_OUT: J5.1; also elsewhere on the board
SCL: J3.5; also elsewhere on the board
SDA: J3.4; also elsewhere on the board

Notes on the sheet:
Connector to RPI
Connector to RF switchboard
SMA Connectors OUT

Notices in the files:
parts and their libraries:
microbuilder: This work is placed in the public domain, and may be freely used for commercial and non-commercial work with the following conditions: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
Eagle_WR-BHD: Copyright: Würth Elektronik
